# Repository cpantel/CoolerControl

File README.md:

# CoolerControl
Cooler speed control for a switch with an ATMega328p

more details: 

https://seguridad-agile.blogspot.com/2020/10/prototipo-de-un-regulador-de.html

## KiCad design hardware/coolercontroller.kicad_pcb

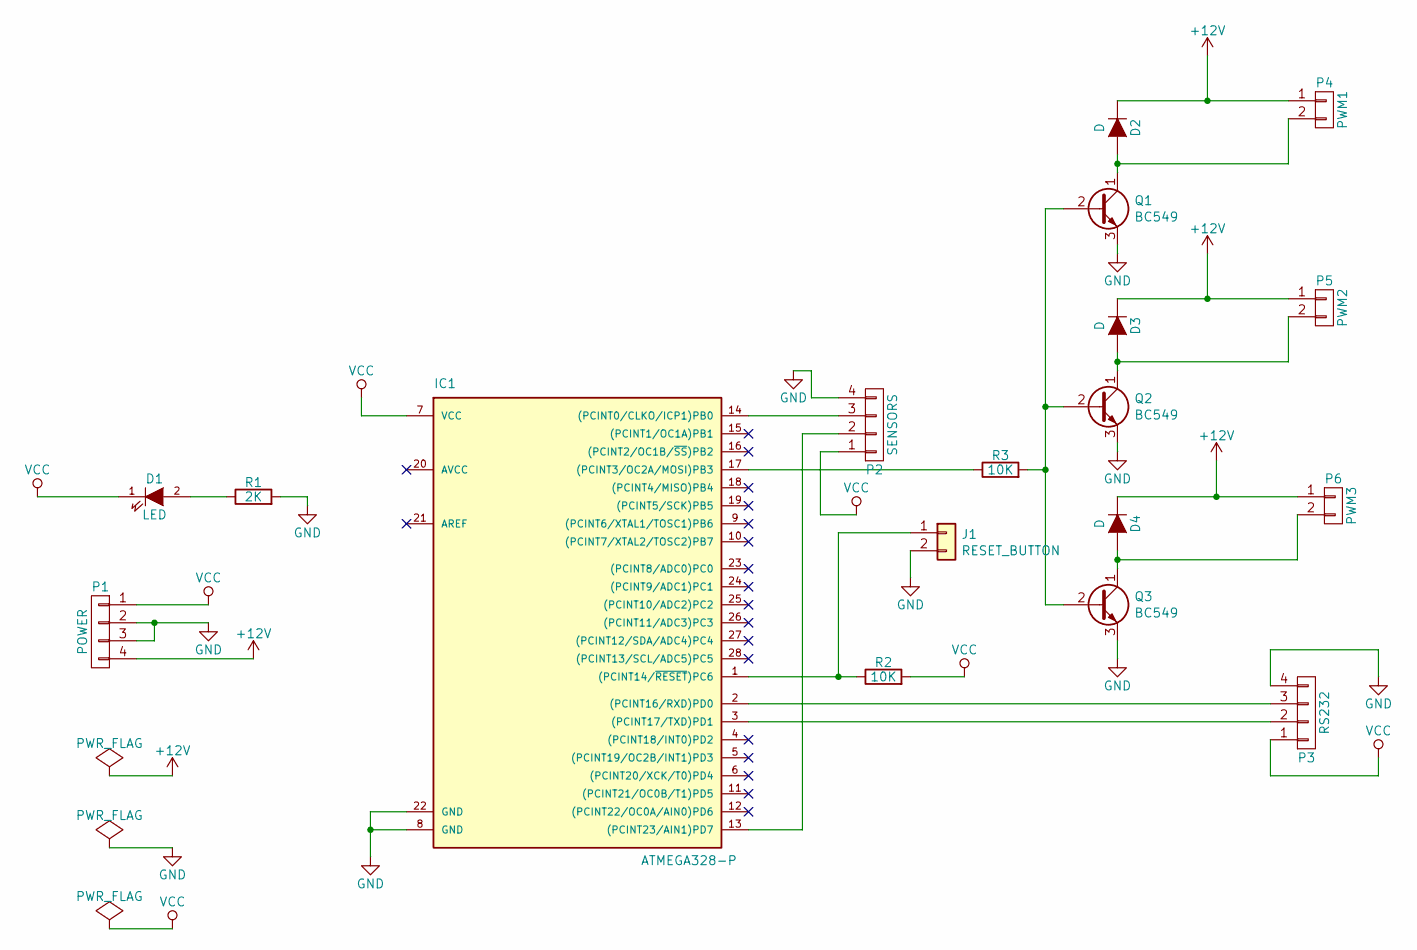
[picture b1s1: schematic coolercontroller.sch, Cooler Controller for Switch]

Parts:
D1: LED; LED_D3.0mm
D2, D3, D4: D; D_5W_P12.70mm_Horizontal
IC1: ATMEGA328-P; DIP-28_W7.62mm
J1: RESET_BUTTON; PinHeader_1x02_P2.54mm_Vertical
P1: POWER; Molex_SPOX_5268-04A_1x04_P2.50mm_Horizontal
P2: SENSORS; PinSocket_1x04_P2.54mm_Vertical
P3: RS232; PinSocket_1x04_P2.54mm_Vertical
P4: PWM1; Molex_KK-254_AE-6410-02A_1x02_P2.54mm_Vertical
P5: PWM2; Molex_KK-254_AE-6410-02A_1x02_P2.54mm_Vertical
P6: PWM3; Molex_KK-254_AE-6410-02A_1x02_P2.54mm_Vertical
Q1, Q2, Q3: BC549; TO-92_Inline
R1: 2K; R_Axial_DIN0309_L9.0mm_D3.2mm_P15.24mm_Horizontal
R2: 10K; R_Axial_DIN0309_L9.0mm_D3.2mm_P15.24mm_Horizontal
R3: 10K; R_Axial_DIN0309_L9.0mm_D3.2mm_P20.32mm_Horizontal

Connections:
+12V: D2.1 (K), D3.1 (K), D4.1 (K), P1.4, P4.1, P5.1, P6.1
GND: IC1.8 (GND), IC1.22 (GND), J1.2, P1.2, P1.3, P2.4, P3.4, Q1.3 (E), Q2.3 (E), Q3.3 (E), R1.2
unnamed: D1.2 (A), R1.1
unnamed: D2.2 (A), P4.2, Q1.1 (C)
unnamed: D3.2 (A), P5.2, Q2.1 (C)
unnamed: D4.2 (A), P6.2, Q3.1 (C)
unnamed: IC1.1 ((PCINT14/~RESET~)PC6), J1.1, R2.1
unnamed: IC1.2 ((PCINT16/RXD)PD0), P3.3
unnamed: IC1.3 ((PCINT17/TXD)PD1), P3.2
unnamed: IC1.13 ((PCINT23/AIN1)PD7), P2.2
unnamed: IC1.14 ((PCINT0/CLKO/ICP1)PB0), P2.3
unnamed: IC1.17 ((PCINT3/OC2A/MOSI)PB3), R3.1
unnamed: Q1.2 (B), Q2.2 (B), Q3.2 (B), R3.2
VCC: D1.1 (K), IC1.7 (VCC), P1.1, P2.1, P3.1, R2.2

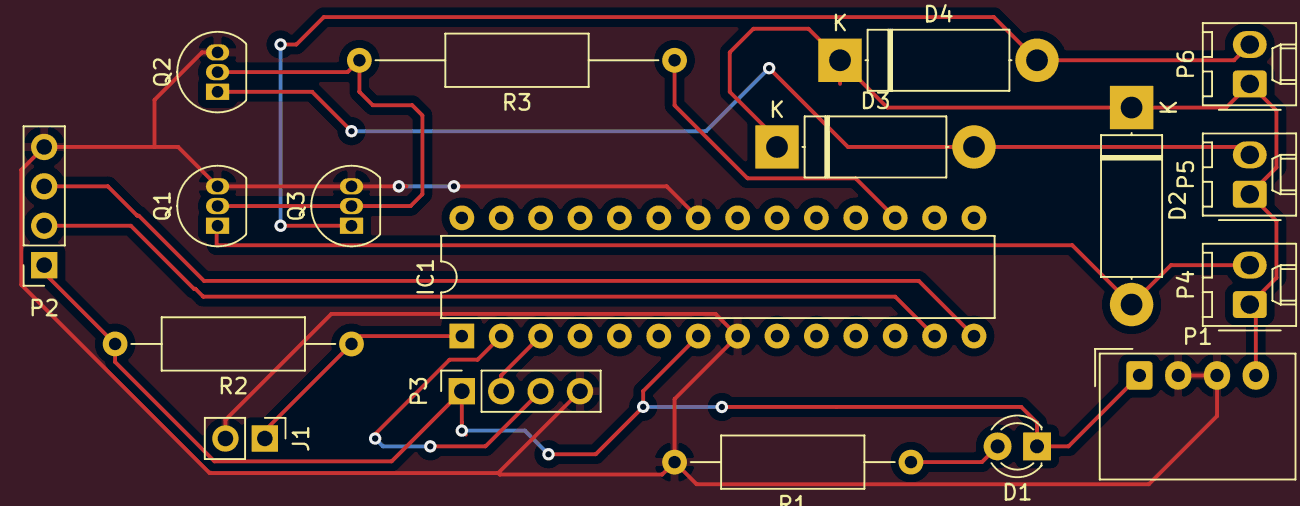
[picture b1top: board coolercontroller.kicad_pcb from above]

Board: 2 copper layers, 18 parts (0 on the bottom side), 14 nets.

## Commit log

2020-07-10 initial commit, working prototype
2020-07-10 cooler on/off behavior and some formatting
2020-07-10 better 127 than 255 when restarting cooler
2020-07-11 fixed new speed function
2020-07-11 changed symlinks due to arduino ide not respecting them
2020-07-11 added config class
2020-07-11 signature to the end of the input as a cancel option
2020-10-07 final tunning
2020-10-14 generate json message instead of csv
2020-10-14 fixed space
2020-10-14 fixed text
